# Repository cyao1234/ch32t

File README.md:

# C32 Devboard

Welp, what else than a tiny c32 devboard? A tiny ch32 device on your fingertips

Features:
- 2 leds
- Low cost
- tiny form
- Nothing much
- USB bootloader via rv003usb
- OPAMPs
- 12 bit ADCs

Everything is also open source, you can see it all in this repo.

The PCB uses a dual layer board in order to save costs, but still maintains a solid ground plane on the back side. It also has an embedded 3v3 ldo.

| Thing | Cost |
| ----- | ---- |
| PCB + PCBA | $115 |

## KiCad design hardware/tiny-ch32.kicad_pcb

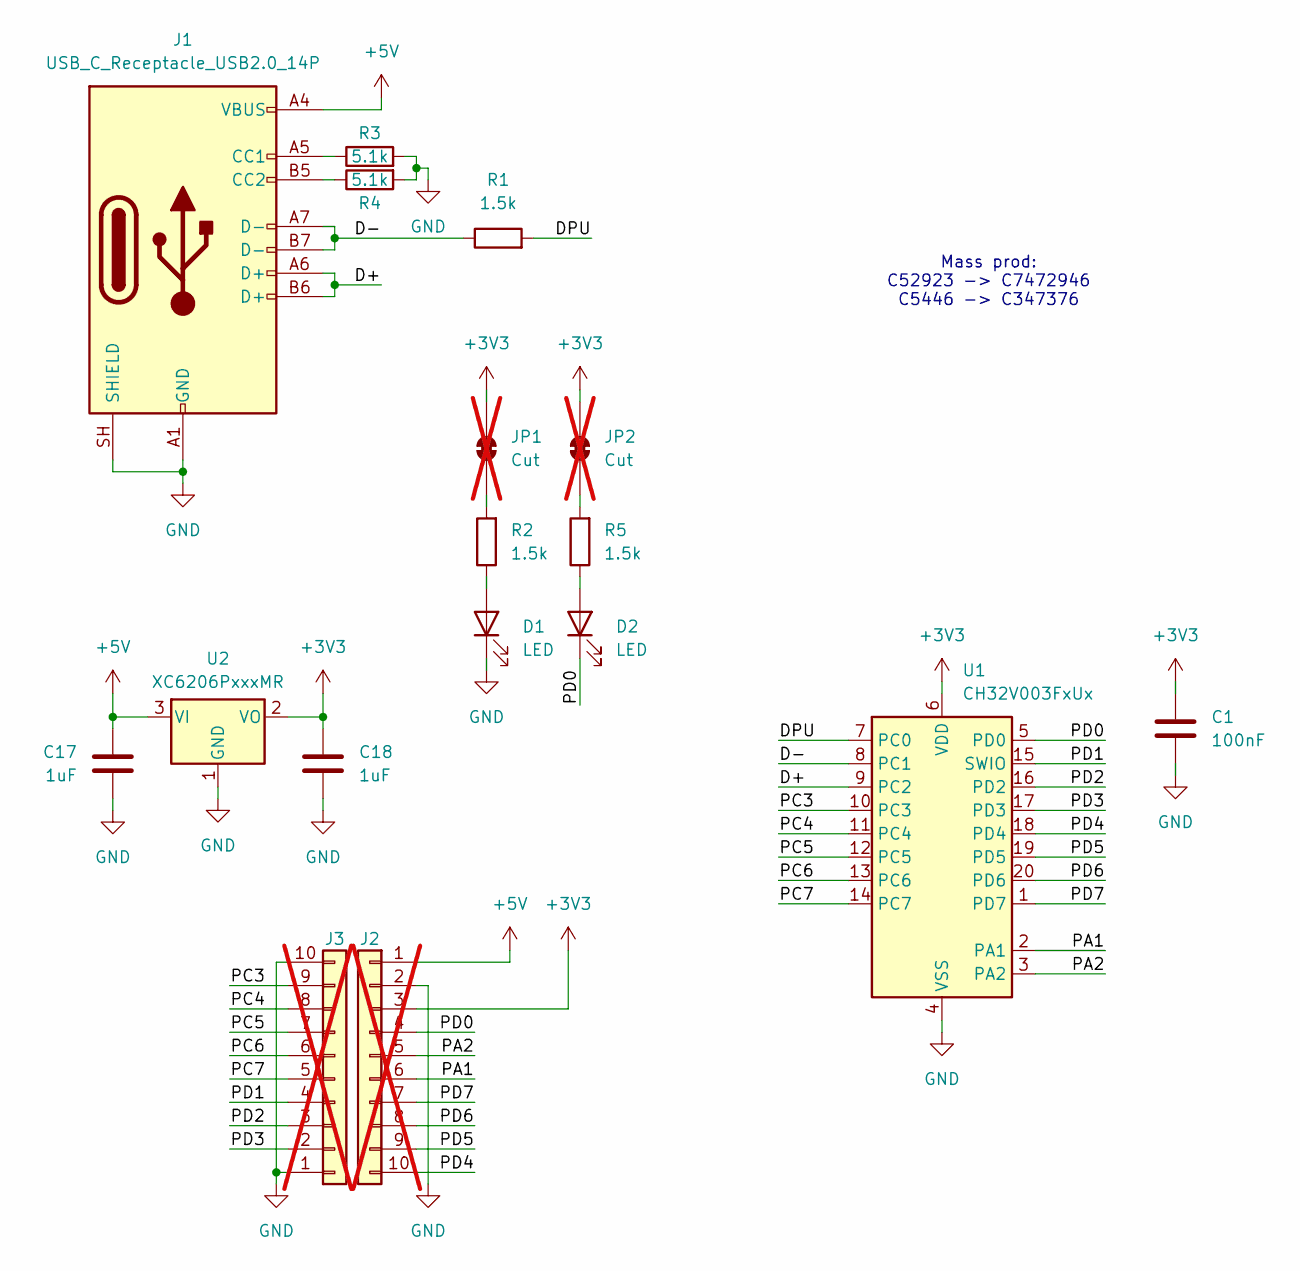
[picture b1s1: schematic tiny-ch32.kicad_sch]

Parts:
C1: 100nF; C_0402_1005Metric; LCSC Part # C307331
C17, C18: 1uF; C_0402_1005Metric; LCSC Part # C52923
D1, D2: LED; LED_0402_1005Metric; LCSC Part # C965793
J1: USB_C_Receptacle_USB2.0_14P; USB_C_Receptacle_HRO_TYPE-C-31-M-12; LCSC Part # C393939
J2, J3: Conn_01x10; Castellated_1x10_P2.54mm_Vertical; not fitted
JP1, JP2: Cut; SolderJumper-2_Bridged_Pad_Small; not fitted
R1, R2, R5: 1.5k; R_0402_1005Metric; LCSC Part # C25867
R3, R4: 5.1k; R_0402_1005Metric; LCSC Part # C25905
U1: CH32V003FxUx; QFN-20-1EP_3x3mm_P0.4mm_EP1.65x1.65mm_ThermalVias; LCSC Part # C5299908
U2: XC6206PxxxMR; SOT-23-3; LCSC Part # C5446

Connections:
+3V3: C1.1, C18.1, J2.3, JP1.1 (A), JP2.1 (A), U1.6 (VDD), U2.2 (VO)
+5V: C17.1, J1.A4 (VBUS), J1.A9 (VBUS), J1.B4 (VBUS), J1.B9 (VBUS), J2.1, U2.3 (VI)
/D+: J1.A6 (D+), J1.B6 (D+), U1.9 (PC2)
/D-: J1.A7 (D-), J1.B7 (D-), R1.1, U1.8 (PC1)
/DPU: R1.2, U1.7 (PC0)
/PA1: J2.6, U1.2 (PA1)
/PA2: J2.5, U1.3 (PA2)
/PC3: J3.9, U1.10 (PC3)
/PC4: J3.8, U1.11 (PC4)
/PC5: J3.7, U1.12 (PC5)
/PC6: J3.6, U1.13 (PC6)
/PC7: J3.5, U1.14 (PC7)
/PD0: D2.1 (K), J2.4, U1.5 (PD0)
/PD1: J3.4, U1.15 (SWIO)
/PD2: J3.3, U1.16 (PD2)
/PD3: J3.2, U1.17 (PD3)
/PD4: J2.10, U1.18 (PD4)
/PD5: J2.9, U1.19 (PD5)
/PD6: J2.8, U1.20 (PD6)
/PD7: J2.7, U1.1 (PD7)
GND: C1.2, C17.2, C18.2, D1.1 (K), J1.A1 (GND), J1.A12 (GND), J1.B1 (GND), J1.B12 (GND), J1.SH (SHIELD), J2.2, J3.1, J3.10, R3.2, R4.2, U1.4 (VSS), U1.21 (VSS), U2.1 (GND)
unnamed: D1.2 (A), R2.1
unnamed: D2.2 (A), R5.1
unnamed: J1.A5 (CC1), R3.1
unnamed: J1.B5 (CC2), R4.1
unnamed: JP1.2 (B), R2.2
unnamed: JP2.2 (B), R5.2

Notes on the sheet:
Mass prod: C52923 -> C7472946 C5446 -> C347376

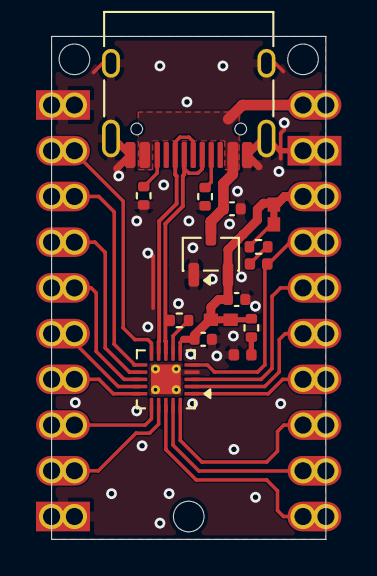
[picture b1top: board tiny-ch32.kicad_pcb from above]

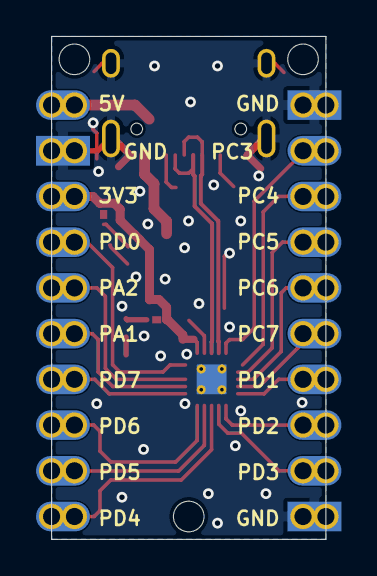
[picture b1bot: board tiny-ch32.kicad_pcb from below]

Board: 2 copper layers, 15.2 x 27.9 mm, 17 parts (2 on the bottom side), 27 nets.

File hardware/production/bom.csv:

Designator,Footprint,Quantity,Value,LCSC Part #
C1,0402,1,100nF,C307331
"C17, C18",0402,2,1uF,C52923 
J1,USB_C_Receptacle_HRO_TYPE-C-31-M-12,1,USB_C_Receptacle_USB2.0_14P,C393939
R1,0402,1,1.5k,C25867
"R3, R4",0402,2,5.1k,C25905
U1,QFN-20-1EP_3x3mm_P0.4mm_EP1.65x1.65mm_ThermalVias,1,CH32V003FxUx,C5299908
U2,SOT-23-3,1,XC6206PxxxMR,C5446

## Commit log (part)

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2026-06-27 Init
